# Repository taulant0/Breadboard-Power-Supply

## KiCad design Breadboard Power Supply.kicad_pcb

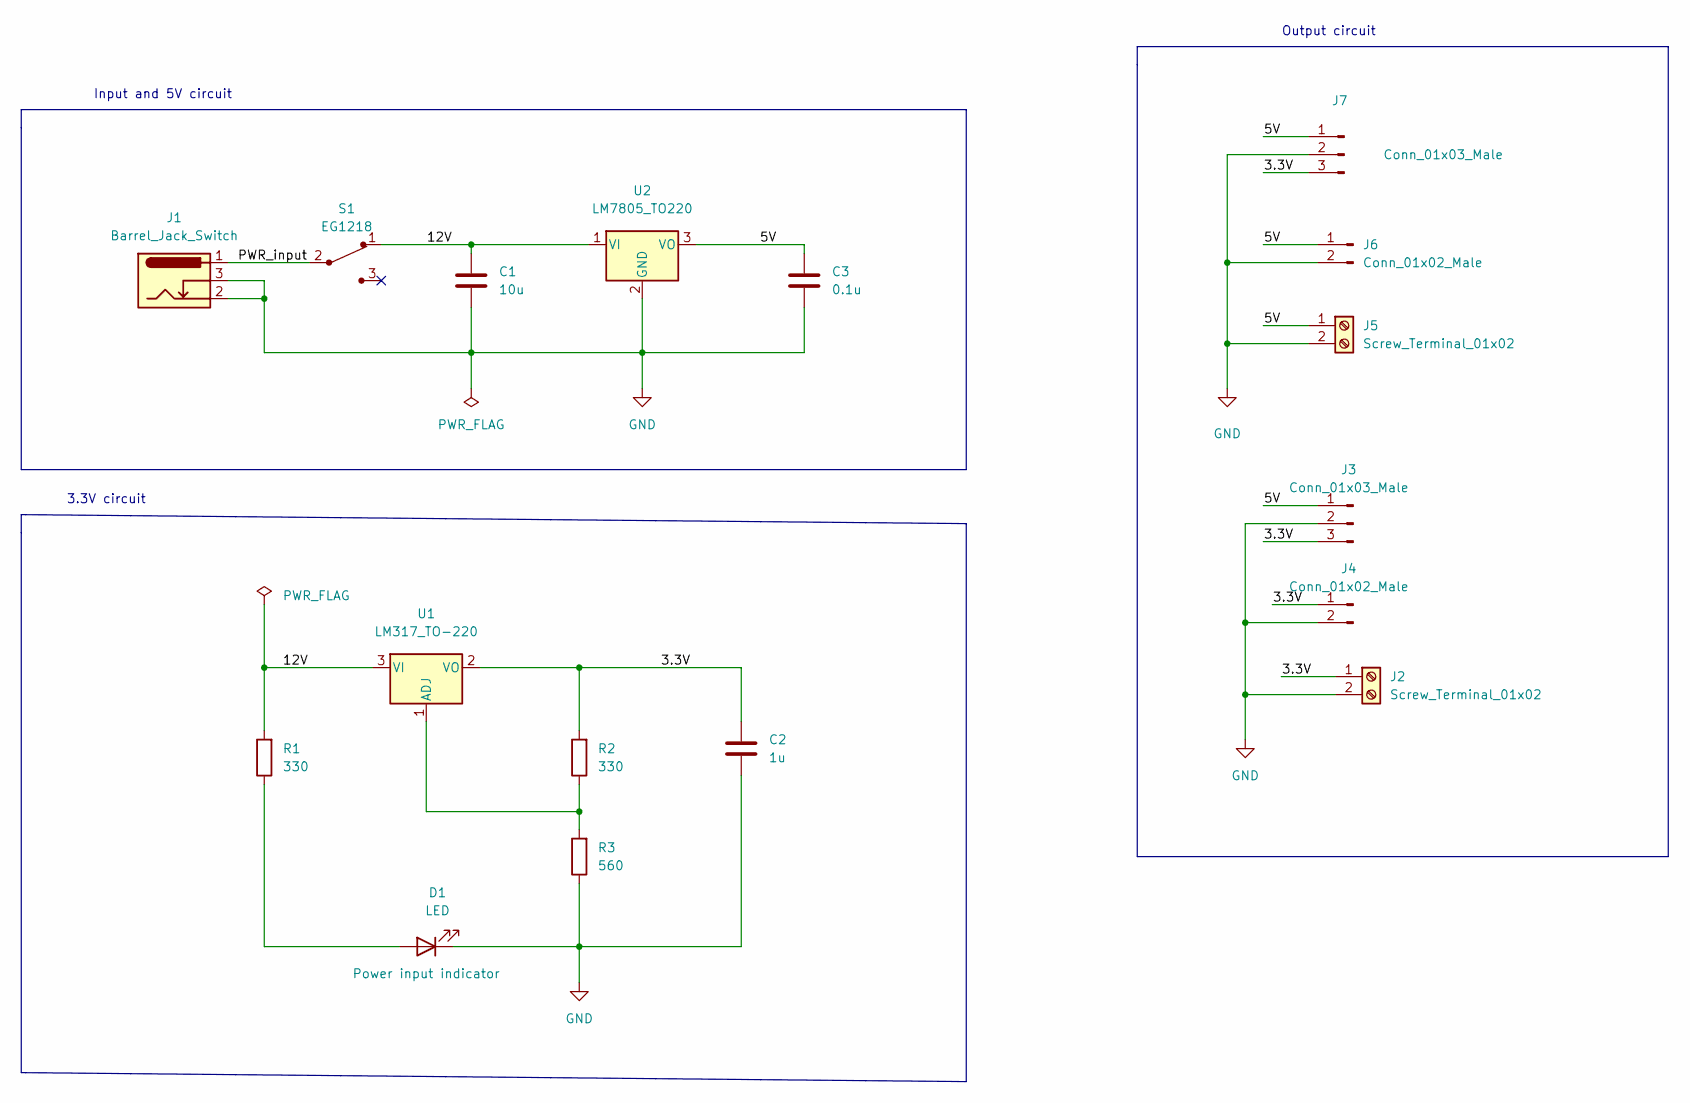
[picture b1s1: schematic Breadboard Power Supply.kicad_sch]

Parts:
C1: 10u; C_Disc_D3.0mm_W1.6mm_P2.50mm
C2: 1u; C_Disc_D3.0mm_W1.6mm_P2.50mm
C3: 0.1u; C_Disc_D3.0mm_W1.6mm_P2.50mm
D1: LED; LED_D5.0mm
J1: Barrel_Jack_Switch; BarrelJack_Horizontal
J2, J5: Screw_Terminal_01x02; TerminalBlock_bornier-2_P5.08mm
J3, J7: Conn_01x03_Male; PinHeader_1x03_P2.54mm_Vertical
J4, J6: Conn_01x02_Male; PinHeader_1x02_P2.54mm_Vertical
R1, R2: 330; R_Axial_DIN0204_L3.6mm_D1.6mm_P7.62mm_Horizontal
R3: 560; R_Axial_DIN0204_L3.6mm_D1.6mm_P7.62mm_Horizontal
S1: EG1218; Switch_Slide_11.6x4mm_EG1218; MPN EG1218; Digi-Key_PN EG1903-ND
U1: LM317_TO-220; TO-220-3_Vertical
U2: LM7805_TO220; TO-220-3_Vertical

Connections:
/3.3V: C2.1, J2.1, J3.3, J4.1, J7.3, R2.2, U1.2 (VO)
/5V: C3.1, J3.1, J5.1, J6.1, J7.1, U2.3 (VO)
/12V: C1.1, R1.2, S1.1, U1.3 (VI), U2.1 (VI)
/PWR_input: J1.1, S1.2
GND: C1.2, C2.2, C3.2, D1.1 (K), J1.2, J1.3, J2.2, J3.2, J4.2, J5.2, J6.2, J7.2, R3.1, U2.2 (GND)
unnamed: D1.2 (A), R1.1
unnamed: R2.1, R3.2, U1.1 (ADJ)

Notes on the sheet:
Output circuit
3.3V circuit
Input and 5V circuit

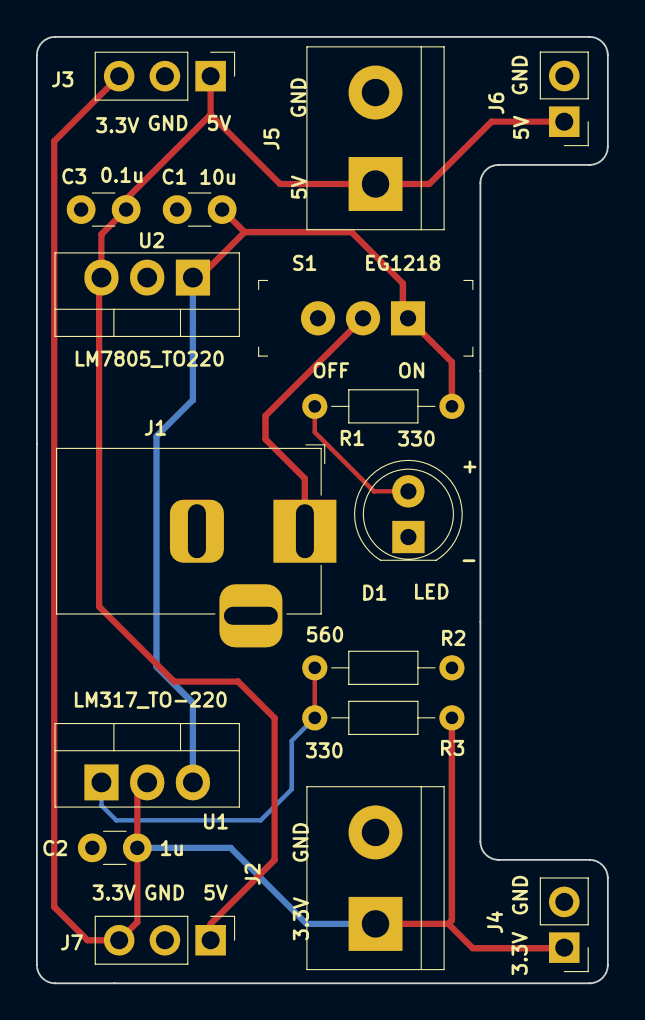
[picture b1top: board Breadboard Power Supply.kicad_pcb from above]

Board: 2 copper layers, 31.7 x 52.6 mm, 17 parts (0 on the bottom side), 7 nets.

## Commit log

2025-05-24 Initial commit - project finished.
2025-05-25 Added the downloadble files.
